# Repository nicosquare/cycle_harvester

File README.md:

# Wat Harvester

Internal behavior of WAT harvester, currently as a project for Embedded Systems - 2017 (2)  cours at Universidad Nacional de Colombia. Also the hardware base of former project in 
IBM's Unchain the Frame hackathon, getting to 4th place among 200 other projects. And finally, it's also the subject of thesis of one of the collaborators in this repo. Open to any 
entushiast or interested. 

## Collaborators:

- Pablo Emilio Camacho Prieto (pecamachop) - pecamachop@unal.edu.co
- Nicolas Mauricio Cuadrado Ávila (nicosquare) - nmcuadradoa@unal.edu.co

## How it works:

The first protype will harvest energy consumption information, basically is a sensor en energy. The hardware consist in an Onion development board mounted in a custom board (ARM 
architecture) that has as peripherals: a Bluetooth communication module and a custom energy sensor. The os of the whole embedded system is ChibiOS, a real time operative system
whose tool-chain allow us to cross-compile towards the Onion board.

## Notes:

Originally the project considered communication via LoRa protocol, very handy with the low frequences we're going to handle, but hardware restriction made us postopone this 
implementation.

# Energy sensor:

An integrated circuit ADE7753 is the core of a single circuit of energy sensoring, based on the recommended common use circuit in the datasheet and on the inverse engineering project
of [NiKiZe](https://github.com/NiKiZe/EMT707CTL). 

## Instructions to clone the repo 

``` git clone https://github.com/nicosquare/wat_harvester.git ```

# TODO

- Define project file structure
- Create dummy project
- Integrate code of Bluetooth module
- Integrate code of energy sensor

Last update: 24 november 2017.

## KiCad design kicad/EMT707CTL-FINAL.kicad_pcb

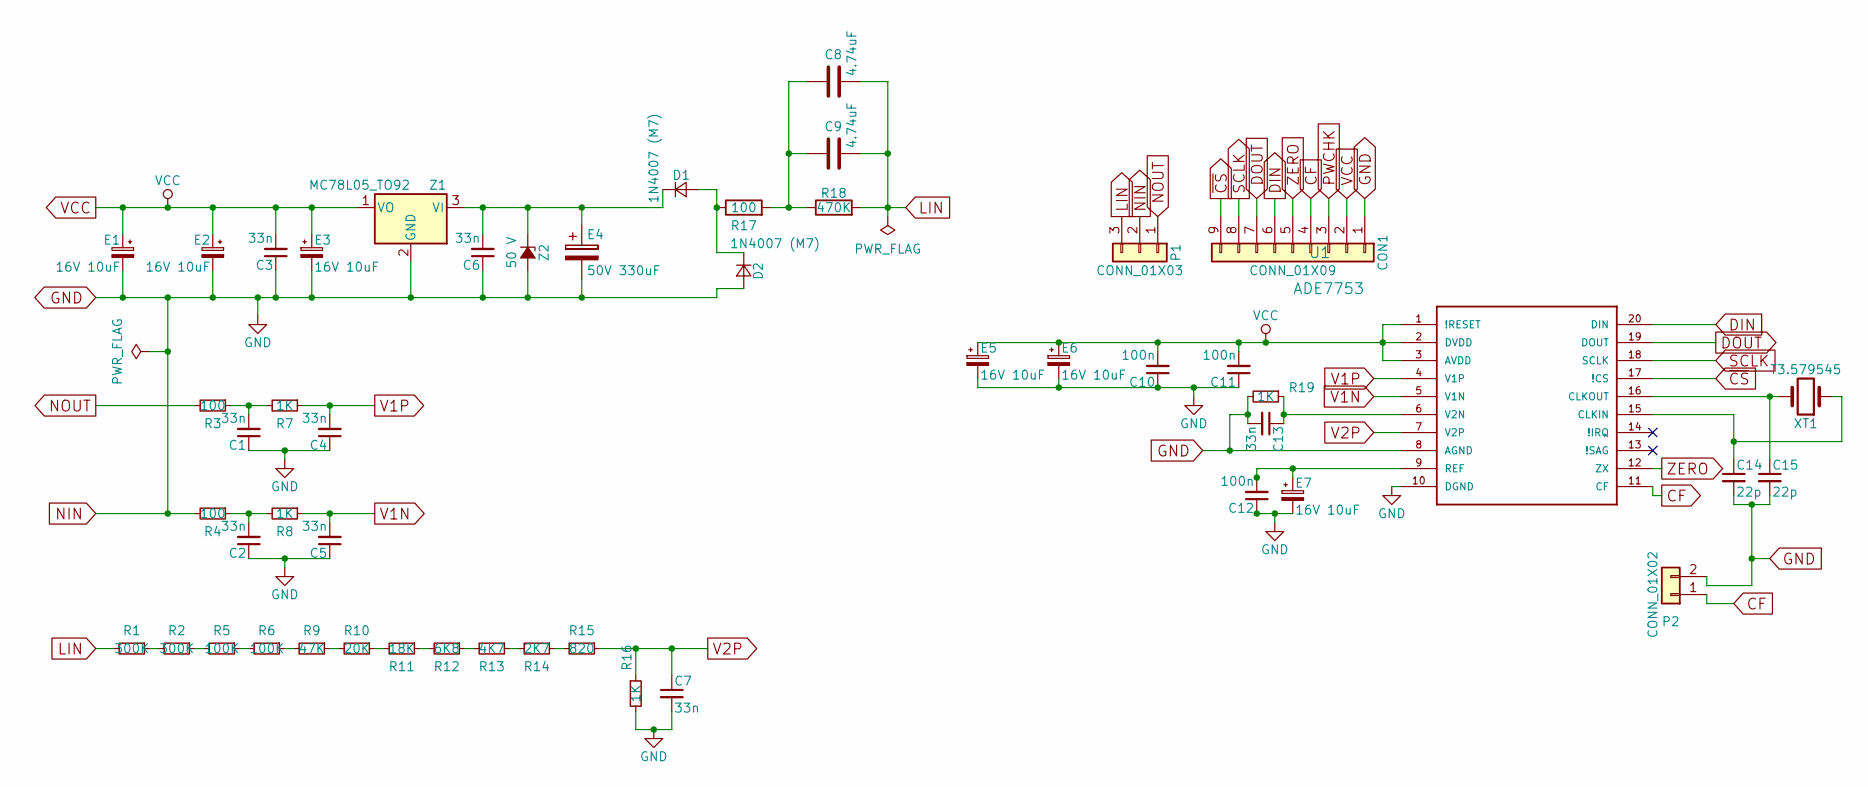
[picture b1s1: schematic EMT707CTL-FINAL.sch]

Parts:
C1, C2, C3, C4, C5, C6, C7, C13: 33n; C_Disc_D3.0mm_W1.6mm_P2.50mm
C8, C9: 4.74uF; C_Axial_L5.1mm_D3.1mm_P10.00mm_Horizontal
C10, C11, C12: 100n; C_Disc_D3.0mm_W1.6mm_P2.50mm
C14, C15: 22p; C_0402
CON1: CONN_01X09; JST_EH_B09B-EH-A_09x2.50mm_Straight
D1, D2: 1N4007 (M7); DO-214AC
E1, E2, E3, E5, E6, E7: 16V 10uF; CP_Elec_4x4.5
E4: 50V 330uF; CP_Elec_10x10
P1: CONN_01X03; JST_EH_B03B-EH-A_03x2.50mm_Straight
P2: CONN_01X02; JST_EH_B02B-EH-A_02x2.50mm_Straight
R1, R2: 300K; R_1206
R3, R4, R17: 100; R_1206
R5, R6: 100K; R_1206
R7, R8, R16, R19: 1K; R_1206
R9: 47K; R_1206
R10: 20K; R_1206
R11: 18K; R_1206
R12: 6K8; R_1206
R13: 4K7; R_0805
R14: 2K7; R_1206
R15: 820; R_1206
R18: 470K; R_1206
U1: ADE7753; SOP65P780X200-20N
XT1: T3.579545; Crystal_HC49-4H_Vertical
Z1: MC78L05_TO92; TO-252-2_Rectifier
Z2: 50 V; D_A-405_P5.08mm_Vertical_KathodeUp

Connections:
CF: CON1.4, P2.1, U1.11 (CF)
DIN: CON1.6, U1.20 (DIN)
DOUT: CON1.7, U1.19 (DOUT)
GND: C1.1, C2.1, C3.1, C4.1, C5.1, C6.1, C7.2, C10.1, C11.1, C12.1, C13.2, C14.2, C15.2, CON1.1, D2.+ (A), E1.2, E2.2, E3.2, E4.2, E5.2, E6.2, E7.2, P1.2, P2.2, R4.2, R16.2, R19.2, U1.8 (AGND), U1.10 (DGND), Z1.2 (GND), Z2.2 (A)
LIN: C8.2, C9.2, P1.3, R1.2, R18.2
NOUT: P1.1, R3.2
unnamed: C1.2, R3.1, R7.2
unnamed: C2.2, R4.1, R8.2
unnamed: C6.2, D1.- (K), E4.1, Z1.3 (VI), Z2.1 (K)
unnamed: C8.1, C9.1, R17.2, R18.1
unnamed: C12.2, E7.1, U1.9 (REF)
unnamed: C13.1, R19.1, U1.6 (V2N)
unnamed: C14.1, U1.15 (CLKIN), XT1.1
unnamed: C15.1, U1.16 (CLKOUT), XT1.2
unnamed: D1.+ (A), D2.- (K), R17.1
unnamed: R1.1, R2.2
unnamed: R2.1, R5.2
unnamed: R5.1, R6.2
unnamed: R6.1, R9.2
unnamed: R10.1, R11.2
unnamed: R9.1, R10.2
unnamed: R11.1, R12.2
unnamed: R12.1, R13.2
unnamed: R13.1, R14.2
unnamed: R14.1, R15.2
PWCHK: CON1.3
SCLK: CON1.8, U1.18 (SCLK)
V1N: C5.2, R8.1, U1.5 (V1N)
V1P: C4.2, R7.1, U1.4 (V1P)
V2P: C7.1, R15.1, R16.1, U1.7 (V2P)
VCC: C3.2, C10.2, C11.2, CON1.2, E1.1, E2.1, E3.1, E5.1, E6.1, U1.1 (!RESET), U1.2 (DVDD), U1.3 (AVDD), Z1.1 (VO)
ZERO: CON1.5, U1.12 (ZX)
~CS: CON1.9, U1.17 (!CS)

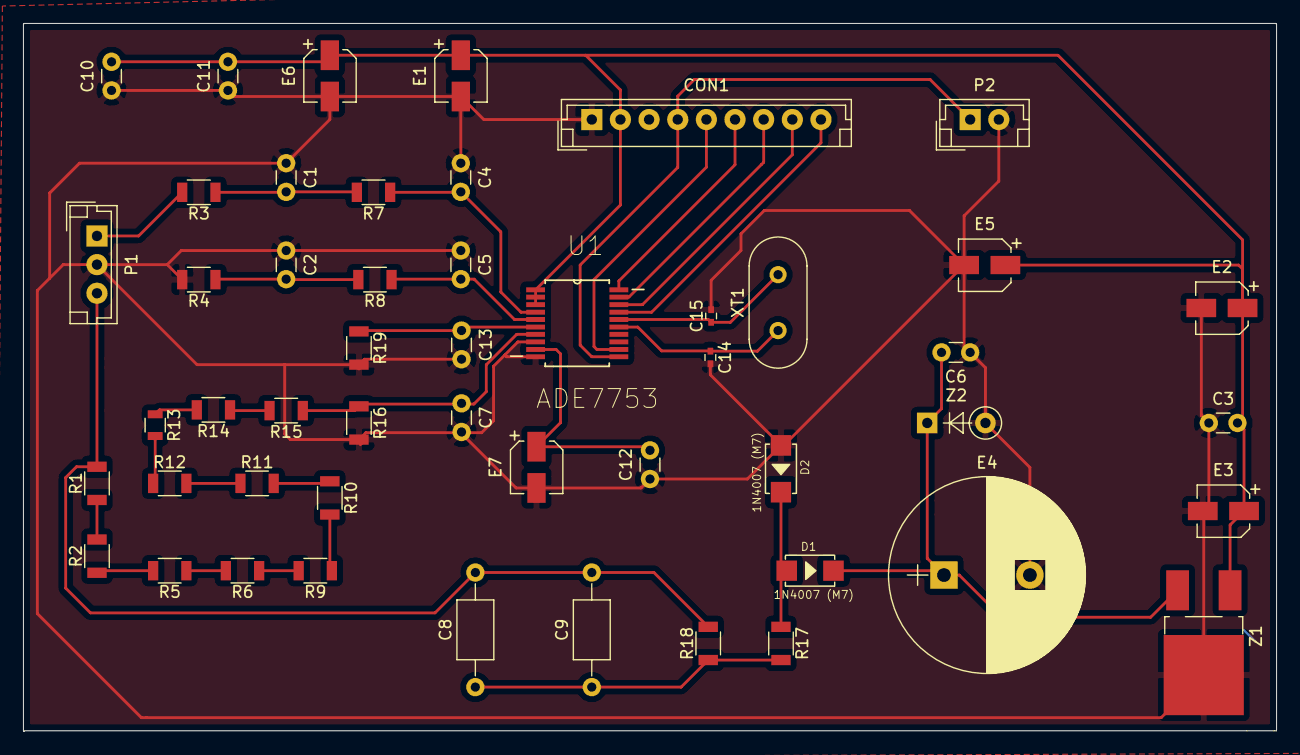
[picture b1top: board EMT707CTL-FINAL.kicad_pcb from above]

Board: 2 copper layers, 109.3 x 61.8 mm, 50 parts (0 on the bottom side), 32 nets.

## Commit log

2017-11-17 Documentation first commit
    A brief of project status.
2017-11-20 Project structure defined
    Makefile changed in order to work externally.
2017-11-24 Blinker working
2017-11-24 Test edition against Pablo
2017-11-24 Modificar fecha
2017-11-24 Fix merge and docs added.
2017-11-24 BT integration with bugs, plan B, ChibiOs 16.1.8
2017-11-26 Bluetooth driver compatible
    Errors on implementation
2017-11-26 Alt project with Chibios 16.1.8
2017-11-27 Chibios 16.1.8 Project with BT libraries
    Project compiling but not tested.
2017-11-27 Folder refactory
    src is now the main project, kicad files added for ADE7753, TODO added.
2017-11-27 Modificación git ignore
2017-11-27 Added img resources folder
2017-11-27 Modify STM32VL folder in Makefile
2017-11-28 Modificaciones BT 27 nov.
2017-11-28 Imgs added to documentation (functional specification)
2017-11-28 Other BT files
2017-11-28 Flowchart of wat harvester
2017-11-28 Serial communication test, BT comm not succesful
2017-11-29 Imagenes
2017-11-29 New BT Driver implentation more clean.
2017-11-29 Sending data BT working and guide comments
2017-11-29 Imagen
2017-11-29 New images for the PCB prototype
2017-11-29 BT image
2018-02-06 Node library for INA219
    Custom library to manage the DC current sensor.
2018-02-06 Corrección Sintaxis JavaScript
2018-02-06 Syntax Review
2018-02-06 Class attribute correction and inclusion of ina219.js file on index.js
2018-02-06 Corrected cast for ints
2018-02-06 Testing ina219.js functions
2018-02-06 Initilizing Variables
2018-02-07 Asynchronous exec problem advances.
2018-02-07 First version of INA219 library
2018-02-07 Changes on interface to test electric measures
